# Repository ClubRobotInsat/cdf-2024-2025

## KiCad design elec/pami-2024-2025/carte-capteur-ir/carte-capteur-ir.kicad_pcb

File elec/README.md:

# Électronique de 2024-2025

Ce dossier contient les cartes utilisées sur le robot et les PAMIs de l'année scolaire 2024-2025.

## Ressources

- [Site de la documentation du club](https://clubrobotinsat.github.io/doc/)

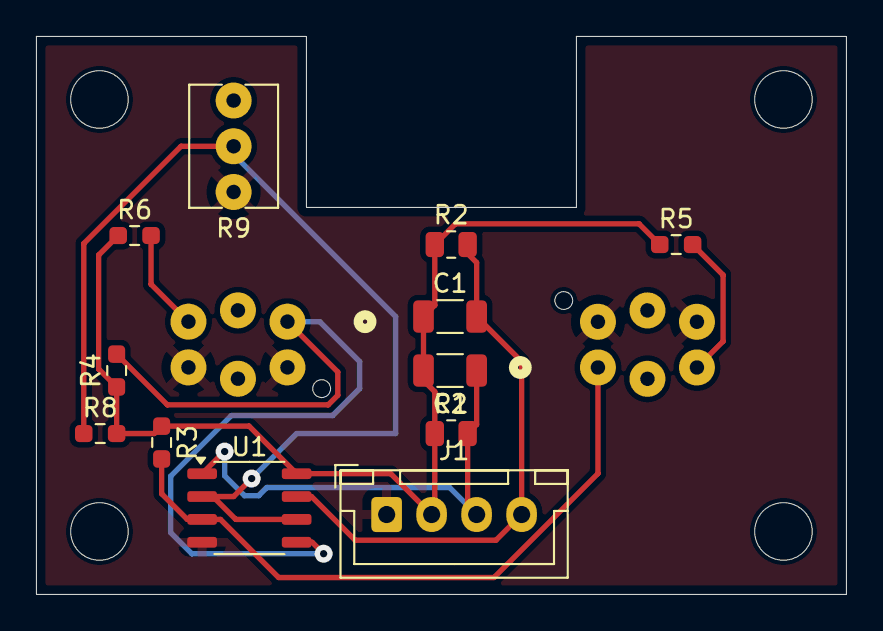
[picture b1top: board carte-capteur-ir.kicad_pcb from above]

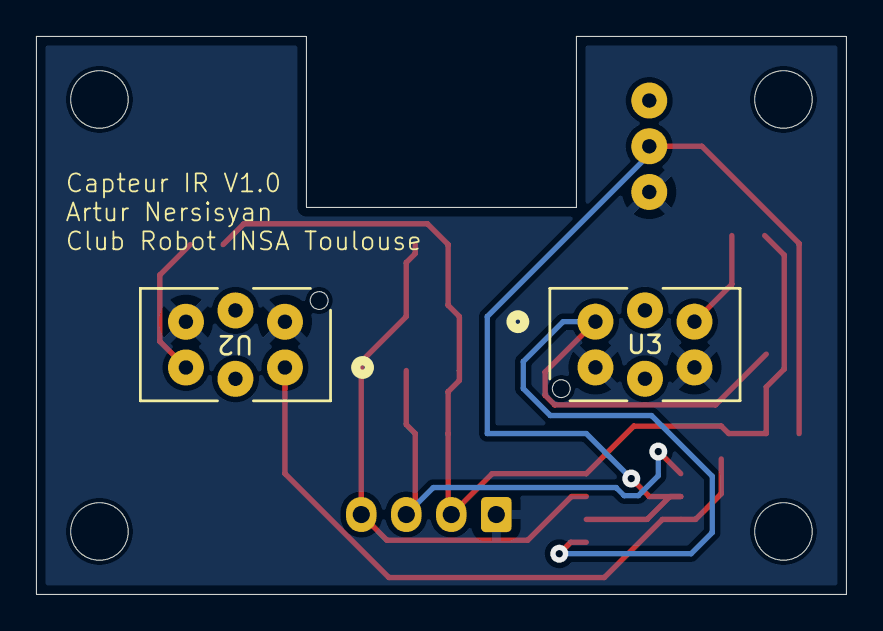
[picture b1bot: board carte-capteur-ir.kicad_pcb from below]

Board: 2 copper layers, 45.0 x 31.0 mm, 14 parts (2 on the bottom side), 9 nets.

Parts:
C1, C2: 470nF; C_1206_3216Metric
J1: Conn_01x04_JST-XH_TCRT5000; JST_XH_B4B-XH-A_1x04_P2.50mm_Vertical
R1, R2: 100k; R_0805_2012Metric
R3, R4, R8: 4700; R_0603_1608Metric_Pad0.98x0.95mm_HandSolder
R5, R6: 330; R_0603_1608Metric_Pad0.98x0.95mm_HandSolder
R9: 10000; Potentiometer_Vishay_T73XW_Horizontal
U1: LM2903; SOP-8_3.9x4.9mm_P1.27mm
U2, U3: TCRT5000; TCRT5000_VIS

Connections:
+5V: C1.1, C2.2, J1.2 (GND), R1.1, R2.1, R3.1, R4.1, R5.1, R6.1, R8.2, U1.8 (V+)
/OUT1: C2.1, J1.3 (TCRT5000_1), R1.2, U1.1
/OUT2: C1.2, J1.4 (TCRT5000_2), R2.2, U1.7
/V_comp: R8.1, R9.2, U1.2 (-), U1.6 (-)
GND: J1.1 (VCC), R9.1, U1.4 (V-), U2.2 (E), U2.4 (C), U3.2 (E), U3.4 (C)
unnamed: R3.2, U1.3 (+), U2.1 (C)
unnamed: R4.2, U1.5 (+), U3.1 (C)
unnamed: R5.2, U2.3 (A)
unnamed: R6.2, U3.3 (A)

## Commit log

2024-12-05 [meca] Proto de carcasse Artur
2024-12-06 Version 3 roues pour le modèles géneriques
2024-12-06 [meca]suppersion de conneries Artur
2024-12-06 [meca] Ajouter 3 roues pour les modèles géneriques
2024-12-06 [meca] suppresion de conneries d'Artur V2
2024-12-06 [meca] ajouter 3 roues test 3
2024-12-06 [meca] Ajouter version 3 roues V4
2025-01-30 Un amalgam mosh
2025-01-30 Revert "Un amalgam mosh"
    This reverts commit b6f5e8f90bc1dd70ccca1bd87a601befbce10968.
2025-01-30 Ca devrait etre bon :)
2025-03-25 Init info and elec-soft
2025-04-19 feat : calculate robot position from encoder data and set up CAN command for encoder odometry
2025-04-21 A new version of robot added, v0.2
2025-04-22 V1.0 of a IR sensor added
2025-04-24 Readme added, repository renamed, card capteur_IR updated
